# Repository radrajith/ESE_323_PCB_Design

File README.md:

## Improved Ammeter Design Project Page

***

### Description

ESE 323 is a Modern Circuit Board Design and Prototyping class taught by Prof Westerfeld. During this class, we are designing circuits using eagle cad software and also designing and building 3d models using Autocad. An Improved current meter will be designed and built for the final project. This current meter design is intended to minimize the effects of burden voltage that is present in the multimeters used in the lab and other facilites. 

***

### design and spec

Design drawing(initial version)

The current meter will be designed to read up to 7A. The maximum current rating is set to be 8A (the fuse will break at this point) and will only be able to read positive DC currents. The circuit can be powered by a battery with a voltage ranging from 2.5 to 5v, in this design 2-AAA battery is used as a power source i.e 3V source. The Analog current measurement will be sampled at 12kSPS (based on atxmega32 specs), and the digital output will have 12-bit resolution. 

The current is read by measuring the voltage that flows across a shunt resistor. The shunt resistor is specially chosen to have current sense technology, where the resistors packs have 4 terminals, 2 for current flow, and 2 for current measurement. The voltage across the resistor is read using the Atxmega micro controller's built in Analog to digital converter(ADC). 
 
Since the class is about coming with our own design and specs, I decided to add some extra feature to make this project cooler. A LCD touch screen is added to display the current readings such as peak, instantaneous, rms etc. In addition the LCD will be used to graph continuous data assuming I will finish the programming on time. Since the programming had to go through a number of revisions, a PDI communication will be implemented to modify the code as intended. In addition to serving as a normal current meter, A USB port will be added to monitor the current usage of mobile phone or other devices charged using USB. A micro usb port will be used as the input and USB as output. 

***

### Ideal World Scenario

The Atxmega32 comes equipped with amplifier of various ranges like 1/2x, 1x,2x,8x...64x. And since the internal bandgap reference voltage is used, the reference voltage will be a constant 1V. This means by using a 0.01 ohm resistor and using a amplification of 1/2x, the max current that can be read using the meter will be 200A. 

*** 

### Design: Considerations and practical limitations

* **Why 7A current limit?**
The 4 terminal  resistors are available for different power rating for 0.01 ohms. For instance, if 5W rated resistor was implemented the maximum current it can handle would be 22.36A (sqrt(5/0.01)). However, larger current required the trace width of the PCB to be more than 0.4 inch/1cm width. Since the board size use for this design is 5cmx5cm, having a trace width of 1cm will require larger board which adds to the cost. In addition the resistor land pattern is quite small that having a trace causes overlaps. A 4mm/.16in trace is implemented in this design, which corresponds to 7-8A according to graph. 

source: https://wiki.xtronics.com/index.php/Wire-Gauge_Ampacity

* **Using 0.5mohm vs 1mohm 4 terminal resistor?**

Although the cost and sizing of both parts remain the same, for this design 0.01 mohm resistor is used. An ammeter ideally has 0 internal resistance, thus for a current meter design its desired to pick a shunt resistor with lowest resistance. However, I had to go with 1mOhm resistor due to the fact that at practical usage, there is resistance contributed from the solder and traces. This will cause error in measurement. In addition, the limitation also arises from the availability of amplifiers in the MCU. With a step voltage of 0.000244, using 0.5 mOhm resistor will reduce the minimum current that can be measured and also accuracy. Thus to have a smaller minimum current, better accuracy and less error a higher valued resistor was implemented.

* **Implementation of two display ports
In addition to a 14 pin header, a 4 pin header is added for i2c communication to provide an alternative display source in case the touch screen display malfunctions and the if the coding cannot be finished on time. 

***

### **Schematic View**

Page one - schematic of the whole circuit with headers, jtag, processor, shunt resistor, fuse, banana plug, usb switches connected and wired according to the requirement.

Page two - Schematic drawing of the switching power supply obtained from texas instruments 

### **Board view**

Board layout

***

### Design rule check and Cam Job

After routing all the parts on the board layout, design rule check had to be used to confirm weather the board meets the requirements. Since Fusion pcb services was planned to be used, the design rule check from seeedstudio was downloaded([DRU link](https://github.com/radrajith/ESE_323_PCB_Design/blob/master/SeeedStudio_2layer_DRU_no_angle_20140221.dru))
After running the design rule check, couple of errors was shown. These errors were mainly becuasue of routing wires or vias close to each other. These errors were fixed and the DRC was repeated until there were no errors. 
 
For the cam job, the cam file provided by the seeedstudio does not include one of the files required by the gerbemerge software, it requires a slight modification. The cam file provided from [seeedstudio website](http://support.seeedstudio.com/knowledgebase/articles/422482-fusion-pcb-order-submission-guidelines) does not generate ".bor" file required for the gerbmerge software. Download the modified cam file from [here](https://github.com/radrajith/ESE_323_PCB_Design/raw/master/Seeed_Gerber_Generater_2-layer.cam). If you choose to modify the cam file provided by seeedstudio by yourself, the instructions are provided after the procedure to create cam files

#### procedure to create cam files

- In order to do the cam process, on the board window click file > cam processor.
- This will open up a window, Click file > open > job

- Locate you cam file downloaded provided in the above paragraph. 

- Click process job. This will create all the files necessary to perform gerbmerge operation(described below) or upload to the pcb printing service. 

##### Modify the cam file by yourself(skip this if you used the cam file provided by me)

- After opening the cam processor with the file downloaded from the seeedstudio [link](http://support.seeedstudio.com/knowledgebase/articles/422482-fusion-pcb-order-submission-guidelines), click "add" button

this will create a duplicate window of drill&holes. 
- Modify the "Section" from 'drill&holes' to 'board outline'
- Change "device" from 'excellon' to 'GERBER_RS274X' in the dropdown menu
- Change the "file" extension from '.txt' to '.bor'
- On the right side list of layer, make sure only '20 dimension' is selected, scroll all the way to the bottom to make sure. 

- Click process job. This will create all the files necessary to perform gerbmerge operation(described below) or upload to the pcb printing service. 

***

### Printed Circuit Board(merged)

With primary goal of reducing the cost, group of 10 students joined and decided to combine the PCBs and place the order. Seeedstudio's PCB printint service was used. The 5 Boards were ordered(minimum quantity), for a 260mmX160mm sized board at the cost of $73.65.  

Front view

Rear view

After obtaining the boards, we carefully analyzed for any errors that were made during the manufacturing process. Luckily all of the board were printed as designed in the eagle.

***

### Gerbmerge

#### **[For information about gerbemerge and tutorial click here](https://radrajith.github.io/gerbmerge/)**

Thank a lot Frank Yee for helping me make the gerbmerge tutorial and actively contributing to it. 

***

### Autodesk Inventor Case design pics 

For the case, there were two designs printed. Althougth the first design fit able to encapsulate the board perfectly, there was some inconveniences when changing the battery and assembling the top cover. [First design pics](https://github.com/radrajith/ESE_323_PCB_Design/blob/gh-pages/initialCAD.md)
The second design was planned to include a slide cover for ease of access to the battery. While programming the LCD screen it was clear that batteries had to be changed often. So accessing battery without disturbing anyother assembly was critical. After designing the first design, it was hard to keep the top case in place, for this reason a door type mechanism was devised and implemented. A stylus slot was added to store when not used, however due to over precision the slot sizing was little small. In addition a hole was added to access Jtag without having to remove the entire board out of the case. Similar to the first design the button press and lever was added to access button present beneath the LCD screen. 

* Circuit Board

* Top case

* Bottom case

* Button press extension

* Button press lever

* battery cover

* Assembled parts view. 

***

### 10 minute video of PCB baking in the oven

To watch the solder melting and skip funny conversation, start at 3.25

[Oven Video](https://goo.gl/photos/HqDbT51zgB6RFGLk8)

***

### finished product

***

### Problems faced and how it was solved

#### TPS63000 switching power supply assembly

The switching power supply package is 3mmx3mm. Since the schematic and the board layout were obtained from texas instruments(webbench), the true size of the pads and the package were not realized until we saw the pcb. Soldering this package was causing the major problem. Since the solder paste used was coarse, the solder paste did not flow thorough the thinnest needles. Multiple approaches were tried and we finally figured out the best way to solder this package.

As seen in the picture below, although the pins look like they are making contact with pad, in reality they were not connecting. This flaw was figured out thanks to the amazing camera and zoom capabilities of the Samsung galaxy S7(the model without the automatical combustion feature). The microscope present in the lab was not able to provide a clear picture. 

* Approach one 
   laying a bead of solder on the pads and hoping the solder mask will repel and prevent bridging. This approach almost never worked.
   
* Approach two

   placing a line of solder on a paper towel, making a knife like stucture using paper and placing the exact amount on the pads. This process was highly time consuming and required patience and skills. [Credits - method invented by Harvey and Ricky]
   
* Approach three (success 100%)
   Instead of relying on the reflow oven to melt the solder paste and make connections, the hot air gun was utilized. Intially the center pad of the SPS was soldered on either using the heatgun or reflow oven(center pad marked in pic 1 below using magenta pen). Once the SPS is correctly placed and firmly secured at the center pad. A bead of solder had to applied on the pins(pic 2). Take a napkin and wipe the SPS all around. Since the package is very small, when the excess is cleaned, a line of solder paste is left handing in the corner(pic 3). Setting the hot air gun to 300 degrees, the hot air was direcly blown on top of the SPS until the solder paste turned shiny(5-10s). Pic 4 shows the clean connection joints made, a amazing zoom skills of Samsung S7. 
   
   Pic 1

   Pic 2

    Pic 3

    Pic 4

#### problem in schematic design

when designing the schematic i had two pages. One containing the sps and other containing the rest. When naming the net for vout of the SPS, i named it +3v3 on one page and 3v3 on the other. When reading the net name in page 2, i misread the + that is used to indicate the location, and name the vcc in page 1 as +3v3. This means there was no connecting present in the board. 

This problem was intially fixed by connecting a wire between Cout and the vcc of the jtag. 

However this fix made the front of my board look ugly. For this reason, i found a via that was coming out on back, and scratched the solder mask off and the metal of the via to make a connection on the back. 

#### Pushbutton placed underneath the LCD

With the ultimate goal of bringing down the cost, the PCB was designed with the least size (5mmx5mm), thus pushbutton had to be buried underneath the lcd screen. To access the pushbutton the lever type mechanism was implemented in the case design (refer to the button lever picture under the autocad inventor design pics). The foced applied on the button press is transferred to the lever and presses the button. 

#### Quakko disaster 
While programming the microprocessor, due to the lcd backlight requiring a lot of current, the battery was draining really quickly. To substitute the battery for a constant voltage source, Quakko power supply was used to supply the voltage. The switching power supply when turned on spiked to large voltage causing the SPS to instantly smoke. Due to this disaster, an additional 10 dollars was added to the BOM to obtain the extra SPS. 

***

### Gain Calculations

Highlighted areas indicate the ADC readings. The gain will decrease as the voltage reading goes over 0.96V. 

***

### Coding

Although major coding is yet to be done, the welcome screen code is currently running on the board. In coming days the touch screen functionality will be implemented along with push button functionality. The ADC code is almost complete, with minor fixes the current meter reading can be done. Ideas for a snake game is partially coded. 
The coding that has been done so far has been included below
[Code](https://github.com/radrajith/ATXMEGA_ILI9341_RGBLCD/tree/master/LCD_ILI9341_ESE_323)

Problems faced and coding experience details will be added in the coming days.

***

### Parts, pinouts, BOM

The detailed picture of the parts used has been seperated into a different page along with the BOM. 
[Parts, pinouts, BOM](https://github.com/radrajith/ESE_323_PCB_Design/blob/gh-pages/partsDetail.md)

Since the order of the 10 people were combined, the link to the Super BOM is also attached below.
[Super BOM](https://docs.google.com/spreadsheets/d/1yWEKycQpd-gtfOP6fBI8lNDqo7oUvL_eeN0UET3jQ1g/edit?usp=sharing)

Once again, credits to Frank Yee for putting together and combining the BOM and also managing the finances.

***

### Cost spent 

* PCB Board

size - 160mmx260mm 

quantity - 5

Cost - $59.92

Shipping - $19.72

Discount - -$5.99

Total  - $73.65

* Digikey order 

66 parts

Cost - $129.87

Shipping - $13.50

Tax - $12.37

Total - $155.74

* Texas Instruments order

TPS63000

Quantity - 10 

Cost - $1.91

Total - $19.10

* Total Money spent 

| Rajith  | 48  |

| Harvey  | 35  |

| Frank   | 31  |

| Thomas  | 32  |

| Ka Wing | 49  |

| Raymond | 29  |

| Jerry   | 27  |

| Daniel  | 40  |

| Juan    | 22  |

| Ricky   | 28  |

|   **total**      | 341 |

overall the total cost of the whole project was $48. If some precautionary measure were taken to avoid the quakko disaster, the cost can be reduced $38. If Easyeda pcb printing service was used, the cost could have been reduced further to $34. 

***

### Course improvement suggestions

* Finer solder paste to be used with the thinnest needle. 
* Encouraging to form groups to bring down the cost of the project
* Deadlines to force student to finish the board designs on time. 
* Warn the students about the package sizing, but dont ban the usage of tiny and impossible package. Lets student make mistakes and force them to come up with good solutions. 
* Good microscope or Samsung galaxy S7 phone available in the lab to obtain a magnified view of the connection in the PCB

***

### Contact
radrajith@gmail.com (2016)

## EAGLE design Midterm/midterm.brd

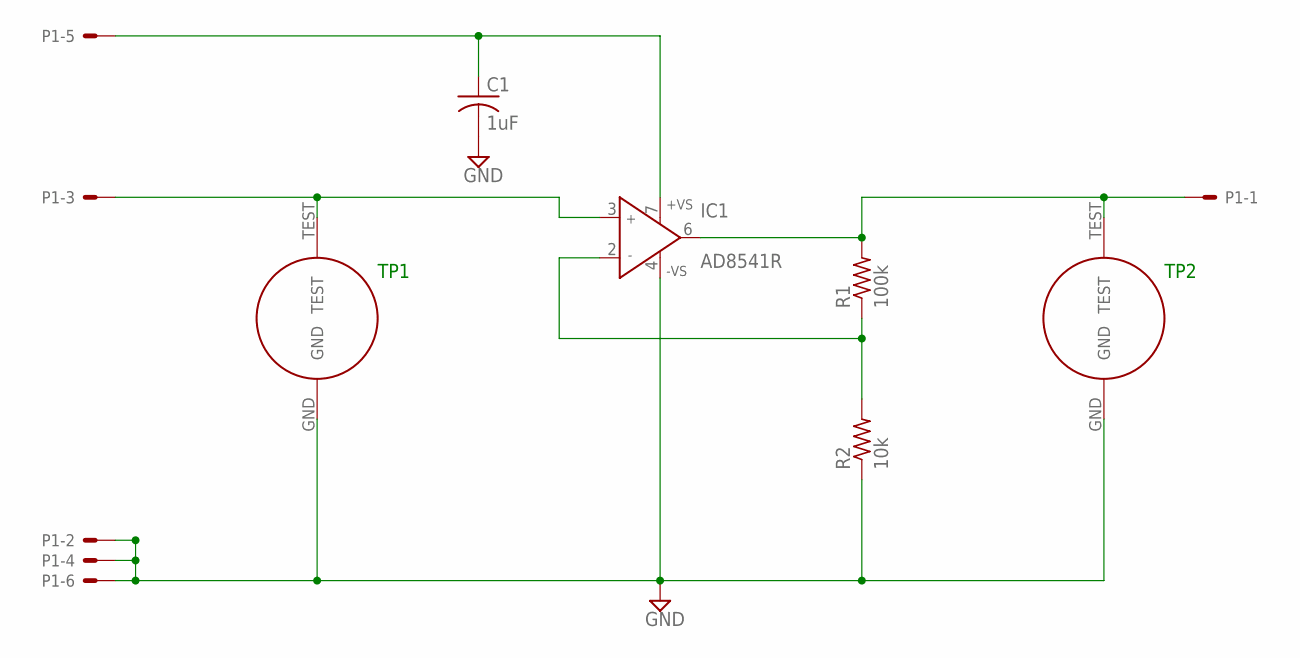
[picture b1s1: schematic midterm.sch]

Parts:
C1: 1uF; C1206
IC1: AD8541R; SO8
P1: 22-23-2061
R1: 100k; M2012
R2: 10k; M2012
TP1, TP2: TEST_POINT

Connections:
GND: C1.2, IC1.4 (-VS), P1.2, P1.4, P1.6, R2.1, TP1.GND, TP2.GND
unnamed: C1.1, IC1.7 (+VS), P1.5
unnamed: IC1.3 (IN+), P1.3, TP1.TEST
unnamed: IC1.2 (IN-), R1.1, R2.2
unnamed: IC1.6 (OUT), P1.1, R1.2, TP2.TEST

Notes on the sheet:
TP1
TP2

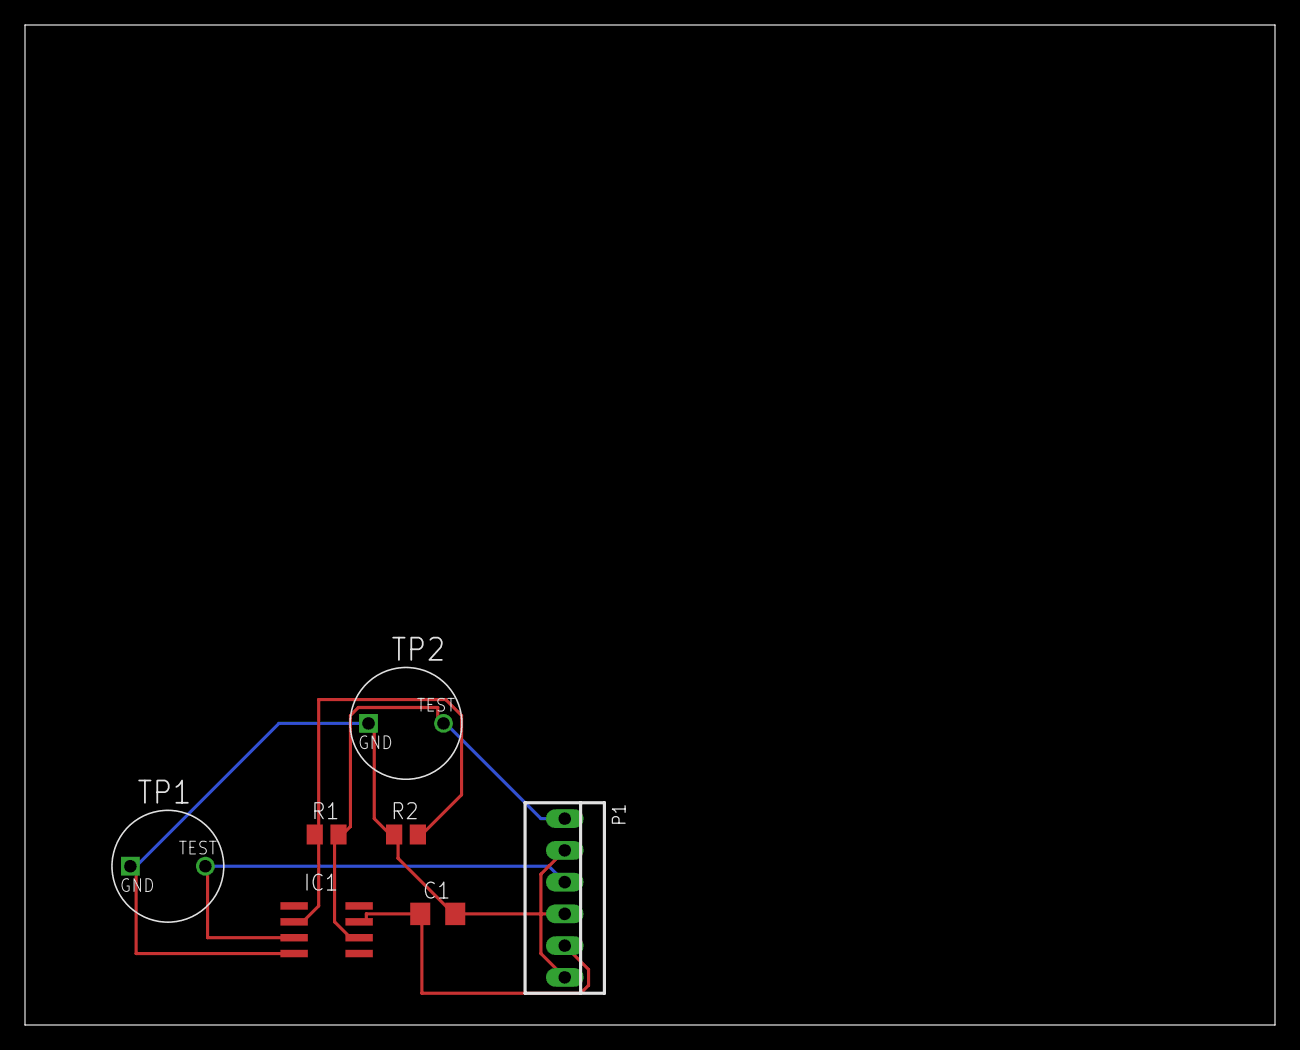
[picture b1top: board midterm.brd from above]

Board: 2 copper layers, 100.0 x 80.0 mm, 7 parts (0 on the bottom side), 5 nets.

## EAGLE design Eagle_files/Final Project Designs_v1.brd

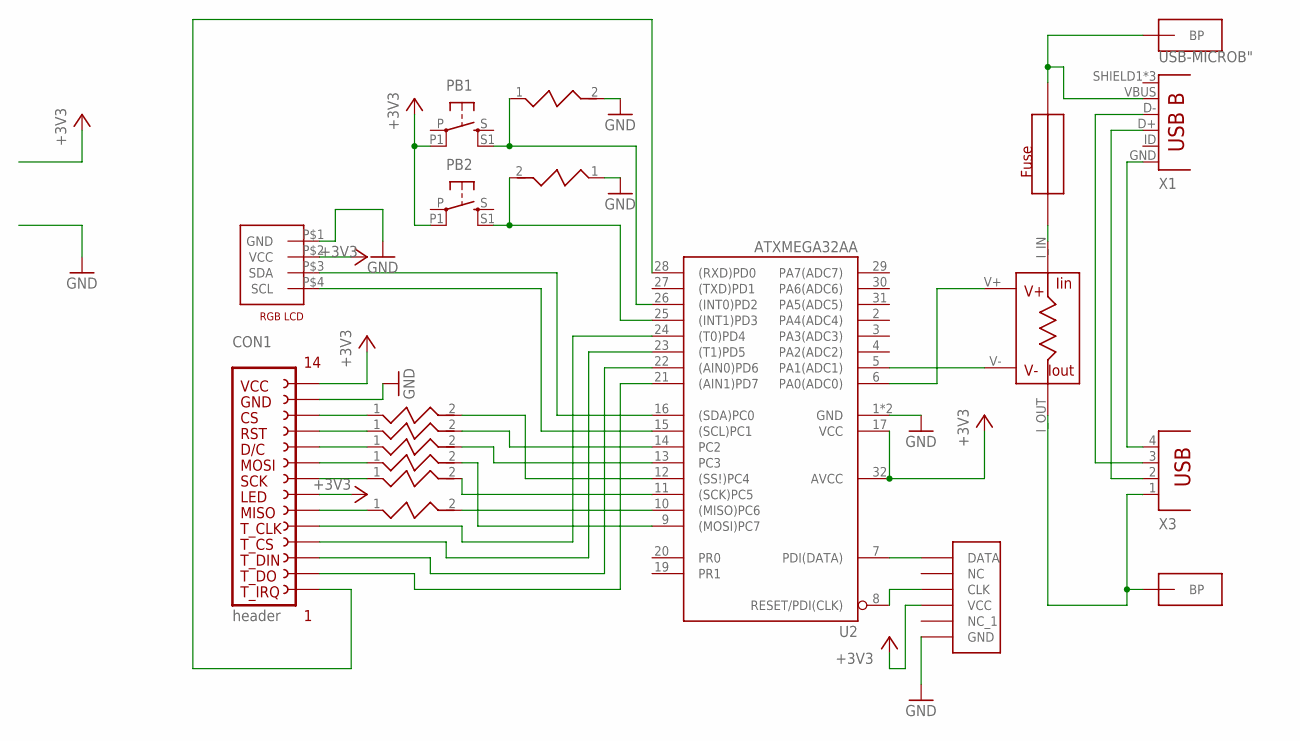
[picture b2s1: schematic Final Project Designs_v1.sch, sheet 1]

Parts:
CON1: header; FE15
CON2: 4PIN_GROVE_CONNECTORUNIVERSAL_4_PIN_CONNECTOR; RGB_LCD
F1: FUSE_SMT
PB1, PB2: 10-XX-4.5SMD; BT4.5X4.5
R1: RESISTOR_4PIN
R2, R3, R4, R5, R6, R7, R8, R9: RESISTOR
U2: ATXMEGA32AA; TQFP32-08
X1: USB-MICROB"; USB-B-MICRO-SMD_V03
X3: PN87520
X4: JTAG
X5, X6: BANANA_PLUG

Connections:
+3V3: CON1.P$7 (LED), CON1.P$14 (VCC), CON2.P$2 (VCC), PB1.P1, PB2.P1, U2.17 (VCC), U2.32 (AVCC), X4.VCC
B$2: R1.I_OUT, X3.1, X5.P$1, X5.P$2
GND: CON1.P$13 (GND), CON2.P$1 (GND), R8.2, R9.1, U2.1 (GND), U2.18 (GND), X4.GND; also elsewhere on the board
unnamed: R5.2, U2.9 ((MOSI)PC7)
unnamed: R6.2, U2.11 ((SCK)PC5)
unnamed: CON1.P$9 (MOSI), R5.1
unnamed: CON2.P$4 (SCL), U2.15 ((SCL)PC1)
unnamed: CON2.P$3 (SDA), U2.16 ((SDA)PC0)
unnamed: X1.GND, X3.4
unnamed: X1.D+, X3.2
unnamed: X1.D-, X3.3
unnamed: PB2.S1, R9.2, U2.25 ((INT1)PD3)
unnamed: PB1.S1, R8.1, U2.26 ((INT0)PD2)
unnamed: R2.2, U2.12 ((SS!)PC4)
unnamed: U2.7 (PDI(DATA)), X4.DATA
unnamed: U2.8 (RESET/PDI(CLK)), X4.CLK
unnamed: R1.V+, U2.6 (PA0(ADC0))
unnamed: R1.V-, U2.5 (PA1(ADC1))
unnamed: F1.P$2, R1.I_IN
unnamed: CON1.P$10 (D/C), R4.1
unnamed: CON1.P$11 (RESET), R3.1
unnamed: CON1.P$6 (MISO), R7.1
unnamed: R7.2, U2.10 ((MISO)PC6)
unnamed: CON1.P$8 (SCK), R6.1
unnamed: CON1.P$12 (CS), R2.1
unnamed: F1.P$1, X1.VBUS, X6.P$1, X6.P$2
unnamed: CON1.P$5 (T_CLK), U2.24 ((T0)PD4)
unnamed: CON1.P$4 (T_CS), U2.23 ((T1)PD5)
unnamed: CON1.P$3 (T_DIN), U2.22 ((AIN0)PD6)
unnamed: CON1.P$2 (T_DO), U2.21 ((AIN1)PD7)
unnamed: R3.2, U2.14 (PC2)
unnamed: R4.2, U2.13 (PC3)
unnamed: CON1.P$1 (T_IRQ), U2.28 ((RXD)PD0)

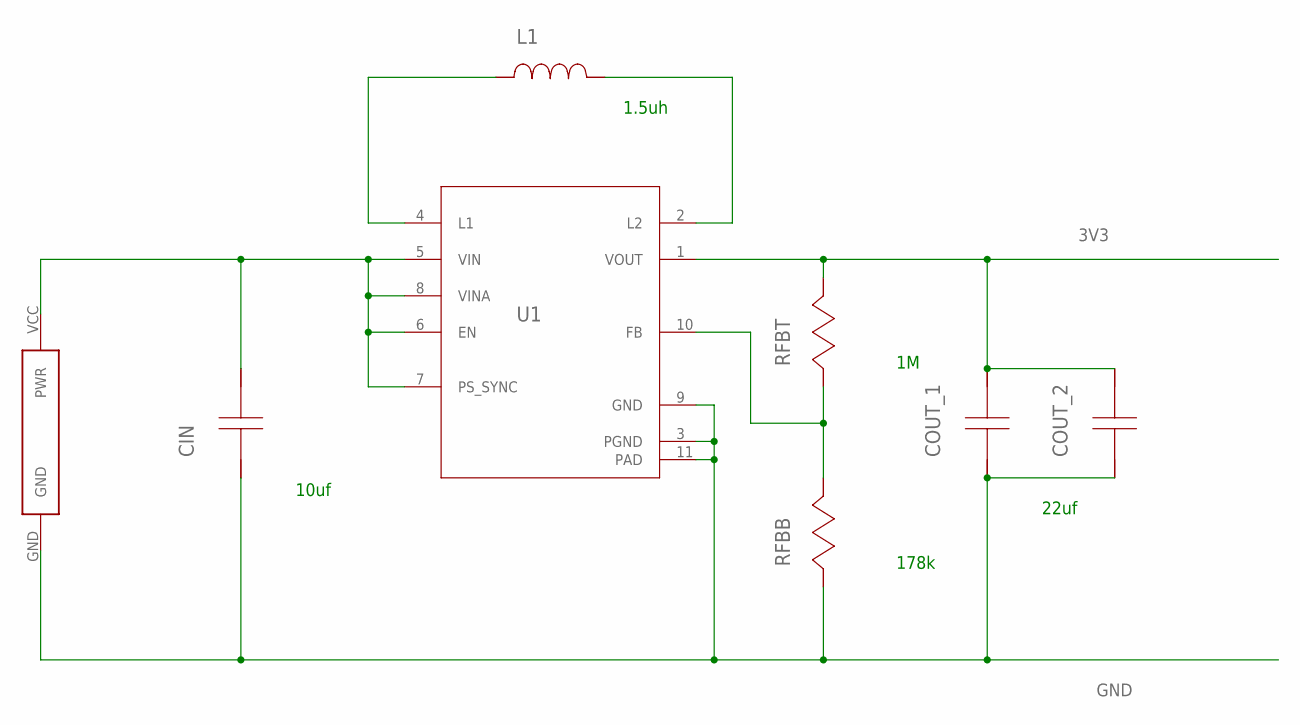
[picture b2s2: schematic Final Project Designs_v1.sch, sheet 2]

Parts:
CIN: LMK212BJ106KG-T; 0805
COUT_1, COUT_2: LMK212BJ226MG-T; 0805
L1: LQM21PN1R5MC0D; 0805
RFBB: CRCW0402178KFKED; 0402
RFBT: CRCW04021M00FKED; 0402
U1: TPS63000DRCR; DRC0010J
U$1: BATTERY

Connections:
2: L1.1, U1.4 (L1)
3V3: COUT_1.1, COUT_2.1, RFBT.1, U1.1 (VOUT)
4: L1.2, U1.2 (L2)
GND: CIN.2, COUT_1.2, COUT_2.2, RFBB.2, U1.3 (PGND), U1.9 (GND), U1.11 (PAD), U$1.GND; also elsewhere on the board
unnamed: RFBB.1, RFBT.2, U1.10 (FB)
VIN: CIN.1, U1.5 (VIN), U1.6 (EN), U1.7 (PS_SYNC), U1.8 (VINA), U$1.VCC (PWR)

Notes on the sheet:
10uf
22uf
1.5uh
178k

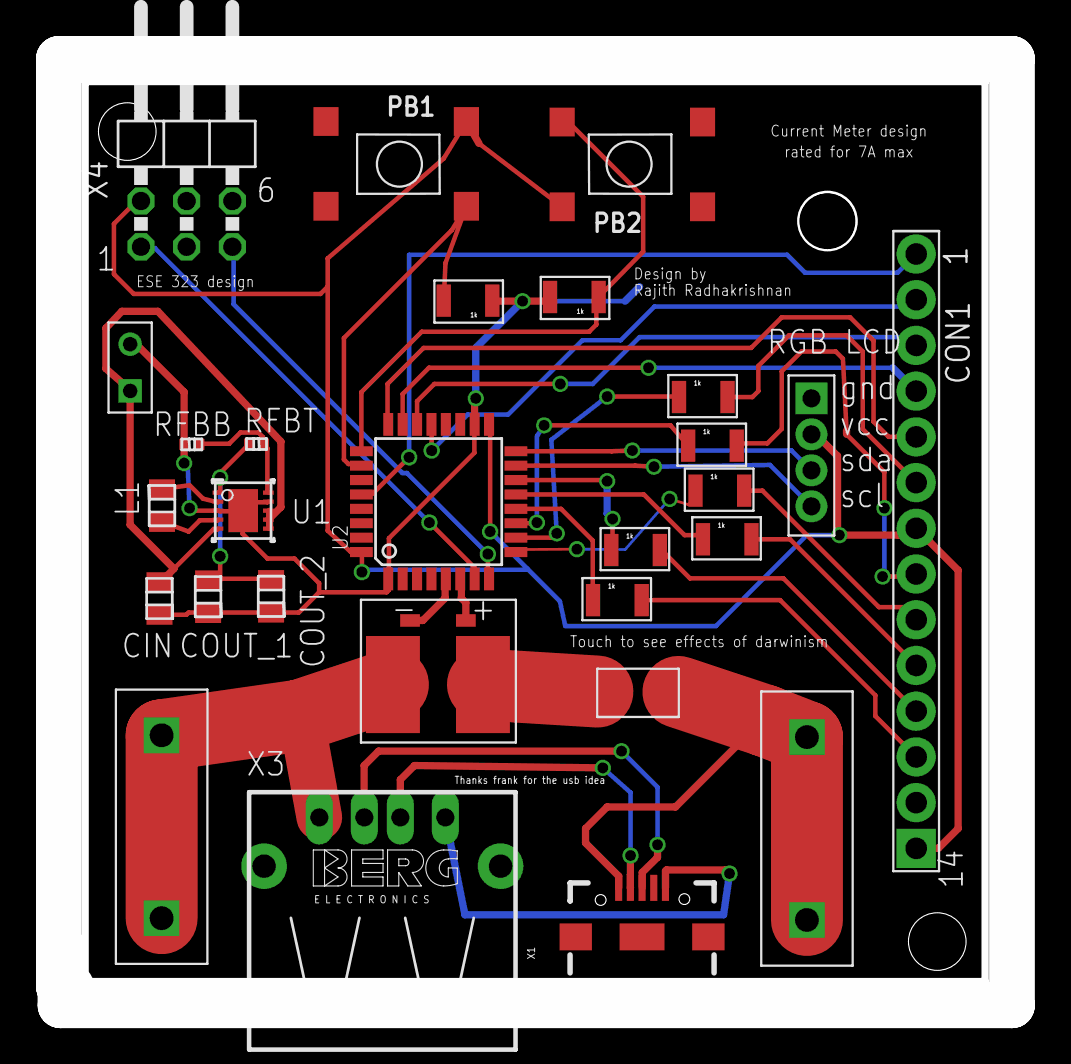
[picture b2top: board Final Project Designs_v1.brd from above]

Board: 2 copper layers, 52.9 x 52.6 mm, 28 parts (0 on the bottom side), 38 nets.

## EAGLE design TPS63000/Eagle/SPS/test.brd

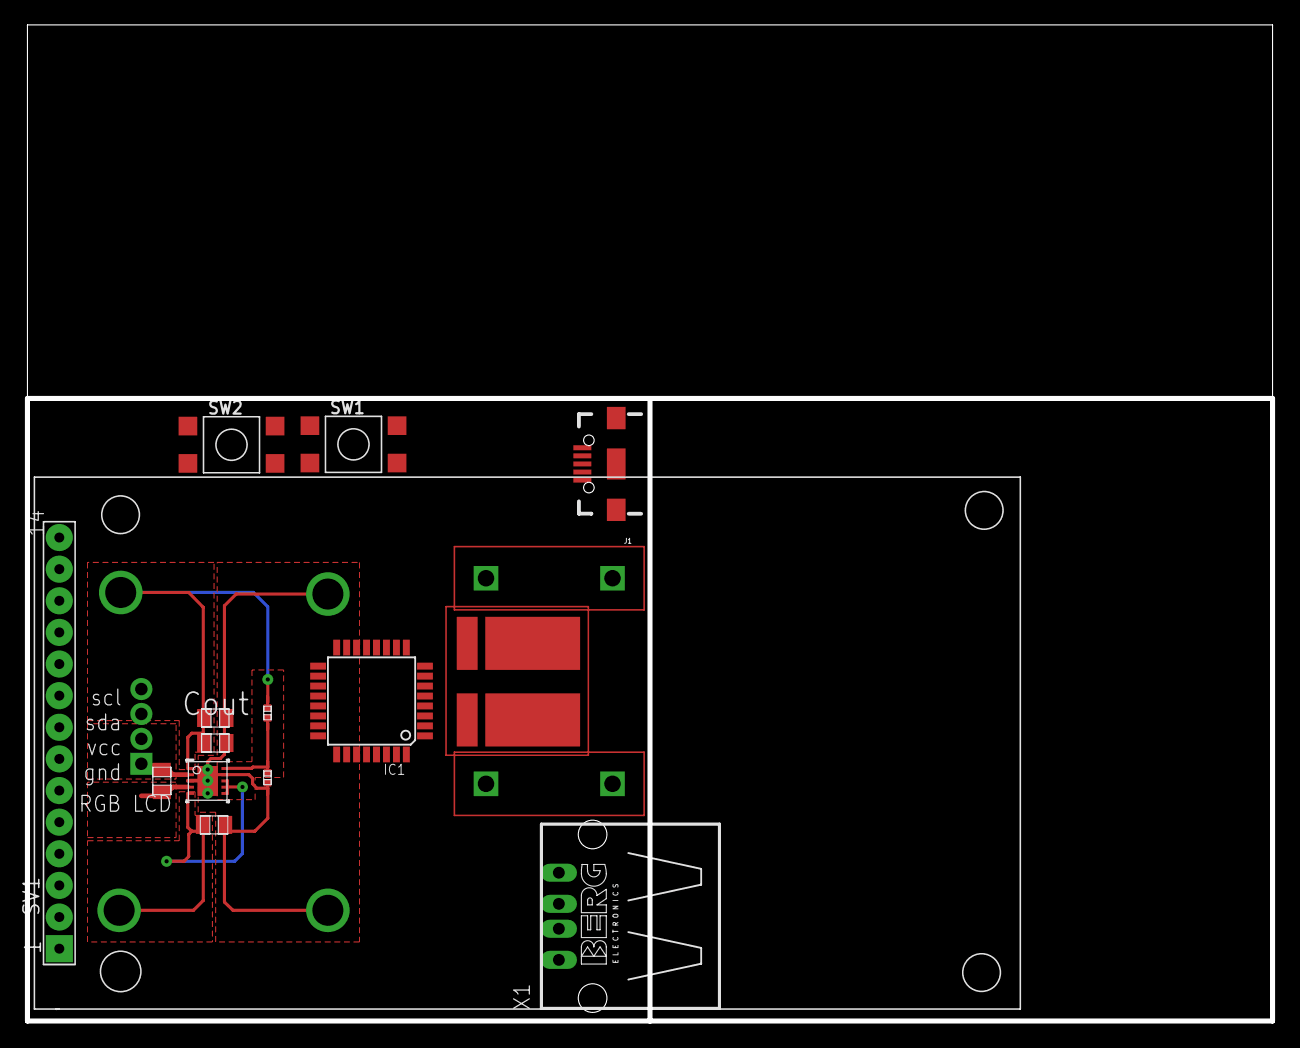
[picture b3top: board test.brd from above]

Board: 4 copper layers, 100.0 x 80.0 mm, 21 parts (0 on the bottom side), 19 nets.

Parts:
CIN: 0805
COUT_1, COUT_2: 0805
E$1, E$2: BANANA_PLUG
GND, GND1: TP-1502
IC1: ATXMEGA32AA; TQFP32-08
J1: USB-MICROB"; USB-B-MICRO-SMD_V03
L1: 0805
RFBB: 0402
RFBT: 0402
SV1: FE15
SW1, SW2: BT4.5X4.5
U1: DRC0010J
U$1: 4PIN_GROVE_CONNECTORUNIVERSAL_4_PIN_CONNECTOR; RGB_LCD
U$2: RESISTOR_4PIN
VIN: TP-1502
VOUT: TP-1502
X1: PN87520

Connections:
0: CIN.2, COUT_1.2, COUT_2.2, GND.1, GND1.1, RFBB.2, U1.3, U1.9, U1.11
3: RFBB.1, RFBT.2, U1.10
6: COUT_1.1, COUT_2.1, RFBT.1, U1.1, VOUT.1
7: L1.1, U1.4
10: L1.2, U1.2
11: CIN.1, U1.5, U1.6, U1.7, U1.8, VIN.1
+3V3: IC1.17, IC1.32, SV1.P$7, SV1.P$14, SW1.P1, SW2.P1, U$1.P$2
GND: IC1.1, IC1.18, SV1.P$13
unnamed: IC1.9, SV1.P$9
unnamed: IC1.10, SV1.P$6
unnamed: IC1.15, U$1.P$4
unnamed: J1.D+, X1.2
unnamed: J1.D-, X1.3
unnamed: IC1.27, SW2.S1
unnamed: IC1.28, SW1.S1
unnamed: E$1.P$1, E$1.P$2, J1.VBUS, U$2.I_IN
unnamed: E$2.P$1, E$2.P$2, U$2.I_OUT, X1.1
unnamed: IC1.6, U$2.V+
unnamed: IC1.5, U$2.V-

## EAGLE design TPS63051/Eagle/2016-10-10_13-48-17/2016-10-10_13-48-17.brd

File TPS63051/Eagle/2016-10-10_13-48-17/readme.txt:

**********************************************************
*************  Important Instructions Follow  ************
**********************************************************

All files exported to: Z:\\46\\52\\4652240\\4\Eagle\2016-10-10_13-48-17\2016-10-10_13-48-17.xml

**********************************************************
*****************Schematic Instructions  *******************
**********************************************************

To import your new Schematic file into Eagle:

1. Unzip the downloaded folder files to local directory and Start Eagle.
2. Select "File"->"Open"->"Schematic..." from the menu at the top of
the screen.
3. Browse to your newly exported file and select the ".sch" file extension.
4. You should now see your schamtic available in Eagle.

**********************************************************
*******************  PCB Instructions  *******************
**********************************************************

To import your new BOARD file into Eagle:

1. Unzip the downloaded folder files to local directory and Start Eagle.
2. Select "File"->"Open"->"Board..." from the menu at the top of
the screen.
3. Browse to your newly exported file and select the ".brd" file extension.
4. Planes will need to be repoured to update the polygon fills
	1. Once your board is loaded and before the repour, the default design rule
	   should be updated for Mask and thermal relief.
		a. Goto Edit and select Design Rules.
			-Select Masks Tab; Set Stop (Min & Max) to 0.0mm
			-Select Supply Tab; Set Thermal Isolation to 0.0mm
	2. To pour the polygon fills, goto Tools and select Ratsnest
	3. The polygons should all be filled now.
5. You should now have an image of your board available in Eagle.

**********************************************************
*******************  LIB Instructions  *******************
**********************************************************

To import your new library into Eagle:

1. Start Eagle.
2. Select "File"->"New"->"Library" from the menu.
3. In the blank library window, select "File" -> "Execute Script"
from the menu.
5. Browse to your newly exported Eagle Script file (".scr" file extension)
6. After opening the file, the script will populate the new library.
Layer 93 should NOT exist.
7. Use "File"->"Save" (or "Save As..") to save the library to the desired
location in Eagle native format.

For additional information, please visit this site:
http://www.accelerated-designs.com/help/Eagle_import.html

You may also find this video helpful:
http://youtu.be/5jGuWY-Yy3Q

**********************************************************
**********************************************************
**********************************************************

Padstack "C1009060090600000P00148P00000" renamed to "C100906009060000"
Component "TPS63051YFFR" renamed to "TPS63051YFFR"
Component "LMK107BBJ106MAHT" renamed to "LMK107BBJ106MAHT"
Component "CL10A106MQ8NNNC" renamed to "CL10A106MQ8NNNC"
Component "CRCW0402100KFKED" renamed to "CRCW0402100KFKED"
Component "CRCW0603100KFKEA" renamed to "CRCW0603100KFKEA"
Component "LQM2HPN1R5MG0L" renamed to "LQM2HPN1R5MG0L"
Component "GRM155R61A102KA01D" renamed to "GRM155R61A102KA01D"
Component "TP-1502" renamed to "TP-1502"

Ultra Librarian Gold 8.1.44 Process Report

Message - Padstack "RX26Y38D0T" Shape(4) is a CIRCLE with no diameter.
Message - Padstack "C100906009060000" Shape(4) is a CIRCLE with no diameter.
Message - Padstack "RX22Y24D0T" Shape(4) is a CIRCLE with no diameter.
Message - Padstack "RX46Y87D0T" Shape(4) is a CIRCLE with no diameter.
Message - Component "TPS63051YFFR" attribute "Datasheet URL" references text style "" that is not in the database.
The default pattern text style "H50s3" was substituted.
Message - Component "TPS63051YFFR" attribute "Frequency" references text style "" that is not in the database.
The default pattern text style "H50s3" was substituted.
Message - Component "TPS63051YFFR" attribute "Imax" references text style "" that is not in the database.
The default pattern text style "H50s3" was substituted.
Message - Component "TPS63051YFFR" attribute "Package" references text style "" that is not in the database.
The default pattern text style "H50s3" was substituted.
Message - Component "TPS63051YFFR" attribute "Mktg_Package" references text style "" that is not in the database.
The default pattern text style "H50s3" was substituted.
Message - Component "TPS63051YFFR" attribute "NSID" references text style "" that is not in the database.
The default pattern text style "H50s3" was substituted.
Message - Component "CRCW0402100KFKED" attribute "Resistance" references text style "" that is not in the database.
The default pattern text style "H50s3" was substituted.
Message - Component "CRCW0402100KFKED" attribute "Power" references text style "" that is not in the database.
The default pattern text style "H50s3" was substituted.
Message - Component "CRCW0402100KFKED" attribute "Tolerance" references text style "" that is not in the database.
The default pattern text style "H50s3" was substituted.
Message - Component "CRCW0603100KFKEA" attribute "Resistance" references text style "" that is not in the database.
The default pattern text style "H50s3" was substituted.
Message - Component "CRCW0603100KFKEA" attribute "Power" references text style "" that is not in the database.
The default pattern text style "H50s3" was substituted.
Message - Component "CRCW0603100KFKEA" attribute "Tolerance" references text style "" that is not in the database.
The default pattern text style "H50s3" was substituted.
Message - Component "LQM2HPN1R5MG0L" attribute "L" references text style "" that is not in the database.
The default pattern text style "H50s3" was substituted.
Message - Component "LQM2HPN1R5MG0L" attribute "DCR" references text style "" that is not in the database.
The default pattern text style "H50s3" was substituted.
Message - Component "LQM2HPN1R5MG0L" attribute "IDC" references text style "" that is not in the database.
The default pattern text style "H50s3" was substituted.
Message - Component "GRM155R61A102KA01D" attribute "Cap" references text style "" that is not in the database.
The default pattern text style "H50s3" was substituted.
Message - Component "GRM155R61A102KA01D" attribute "ESR" references text style "" that is not in the database.
The default pattern text style "H50s3" was substituted.
Message - Component "GRM155R61A102KA01D" attribute "IRMS" references text style "" that is not in the database.
The default pattern text style "H50s3" was substituted.
Message - Component "GRM155R61A102KA01D" attribute "VDC" references text style "" that is not in the database.
The default pattern text style "H50s3" was substituted.

TextStyle count:  24
Padstack count:   8
Pattern count:    5
Symbol count:     5
Component count:  8

Export

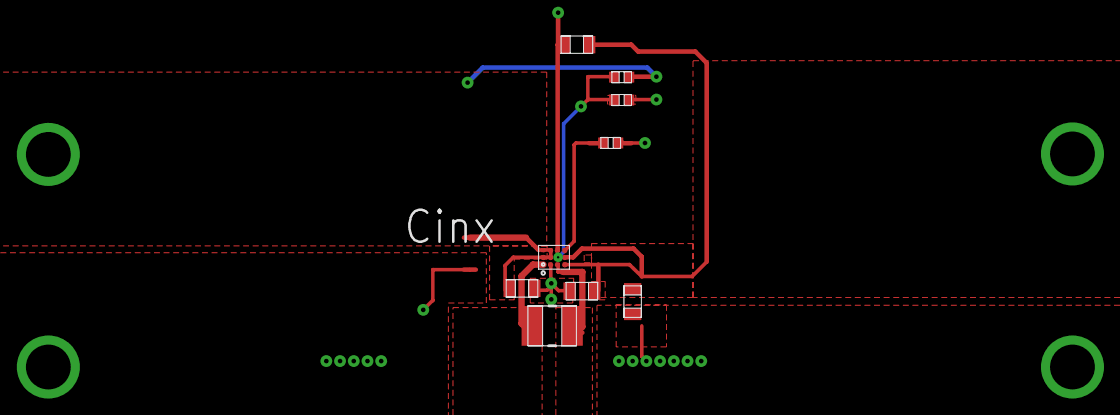
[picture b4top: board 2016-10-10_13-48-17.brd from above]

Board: 4 copper layers, 13 parts (0 on the bottom side), 7 nets.

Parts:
Cin: 0603
Cout: 0603
Coutx: 0603
Css: 0402
GND1, GND2: TP-1502
L1: 1008
Rpfm: 0402
Rpg: 0603
Rpwm: 0402
U1: YFF0012AFAF
VIN: TP-1502
VOUT: TP-1502

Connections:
0: Cin.2, Cout.2, Coutx.2, Css.2, GND1.1, GND2.1, Rpfm.1, Rpfm.2, Rpwm.2, U1.4, U1.8
2: Cin.1, Rpwm.1, U1.2, U1.3, U1.5, U1.6, VIN.1
3: Css.1, U1.12
4: Cout.1, Coutx.1, Rpg.1, U1.10, U1.11, VOUT.1
5: L1.1, U1.1
6: L1.2, U1.7
8: Rpg.2, U1.9

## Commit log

2016-10-09 :boom::camel: Added .gitattributes & .gitignore files
2016-10-09 uploading all files
    uploading all the work done until 10/08/16
2016-10-09 uploading eagle files
2016-10-09 Create gh-pages branch via GitHub
2016-10-09 adding icon picture
2016-10-09 updating icon image
2016-10-09 adding picture of lcd screen
2016-10-09 uploading parts list as csv
2016-10-09 added html compatible BOM file. removed the csv file
2016-10-09 adding hover popup for parts images
2016-10-09 added hover info for TFT lcd display
2016-10-09 changing picture size
2016-10-10 making the csv file to make the github website
2016-10-10 adding pictures of connectors
2016-10-10 added pictures to 14 pin and 4 pin connector
2016-10-11 changed the swtiching power supply and added pics
2016-10-11 Updated BOM
2016-10-11 uploading docs
2016-10-12 Modified 14 pin header to include screw hole layout for lcd
2016-10-13 added more files and datasheets
2016-10-13 add more pics
2016-10-13 gain calculation
2016-10-14 added pictures
2016-10-15 building the schematic
2016-10-15 some datasheets and board modifications
2016-10-17 spreadsheet for the sps
2016-10-18 updated designs
2016-10-20 updated designs, downloaded some datasheets, modified the BOM
2016-10-21 finished the schematic and board designs
2016-10-21 few more changes
2016-10-22 added some files
2016-10-22 files
2016-10-22 gain
2016-10-22 drawing
2016-10-22 included lab 3 report
    updated the webpage
2016-10-23 changed fuse part to a 10A fuse from 15A
2016-10-23 added few more files
2016-10-24 update design and files
2016-10-28 finished everthing
2016-10-29 added DRU and Cam files
2016-11-06 added cad drawings and pictures
2016-11-06 made changes
2016-11-06 pics on cad
2016-11-07 sycncing files
2016-11-07 added pic
2016-11-07 Revert "sycncing files"
    This reverts commit b6d516f6dd6843641752e7c89eda426ca5f2ac01.
2016-11-08 added pics
2016-12-22 Set theme jekyll-theme-architect and migrate Page Generator content
2016-12-22 code changes
2016-12-22 Set theme jekyll-theme-architect
2016-12-22 parts details seperated into different page
2016-12-22 added BOM
2016-12-22 seperated pictures of initial cad designs
2016-12-22 sps pic
2016-12-22 update1
2016-12-22 code changes and pics
2016-12-22 pics
2016-12-22 pics added
2016-12-22 Rename initialCAD.md to initialCAD.html
2016-12-22 Rename initialCAD.html to initialCAD.md
2016-12-22 finished the report
2016-12-22 fixing minor mistake 1
2016-12-22 minor fix 2
2016-12-22 minor fix 3
2016-12-22 minor fix 4
2016-12-22 minor fix 5
2016-12-23 just updating

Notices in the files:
parts and their libraries:
SparkFun-Connectors: Licensing: Creative Commons ShareAlike 4.0 International - https://creativecommons.org/licenses/by-sa/4.0
